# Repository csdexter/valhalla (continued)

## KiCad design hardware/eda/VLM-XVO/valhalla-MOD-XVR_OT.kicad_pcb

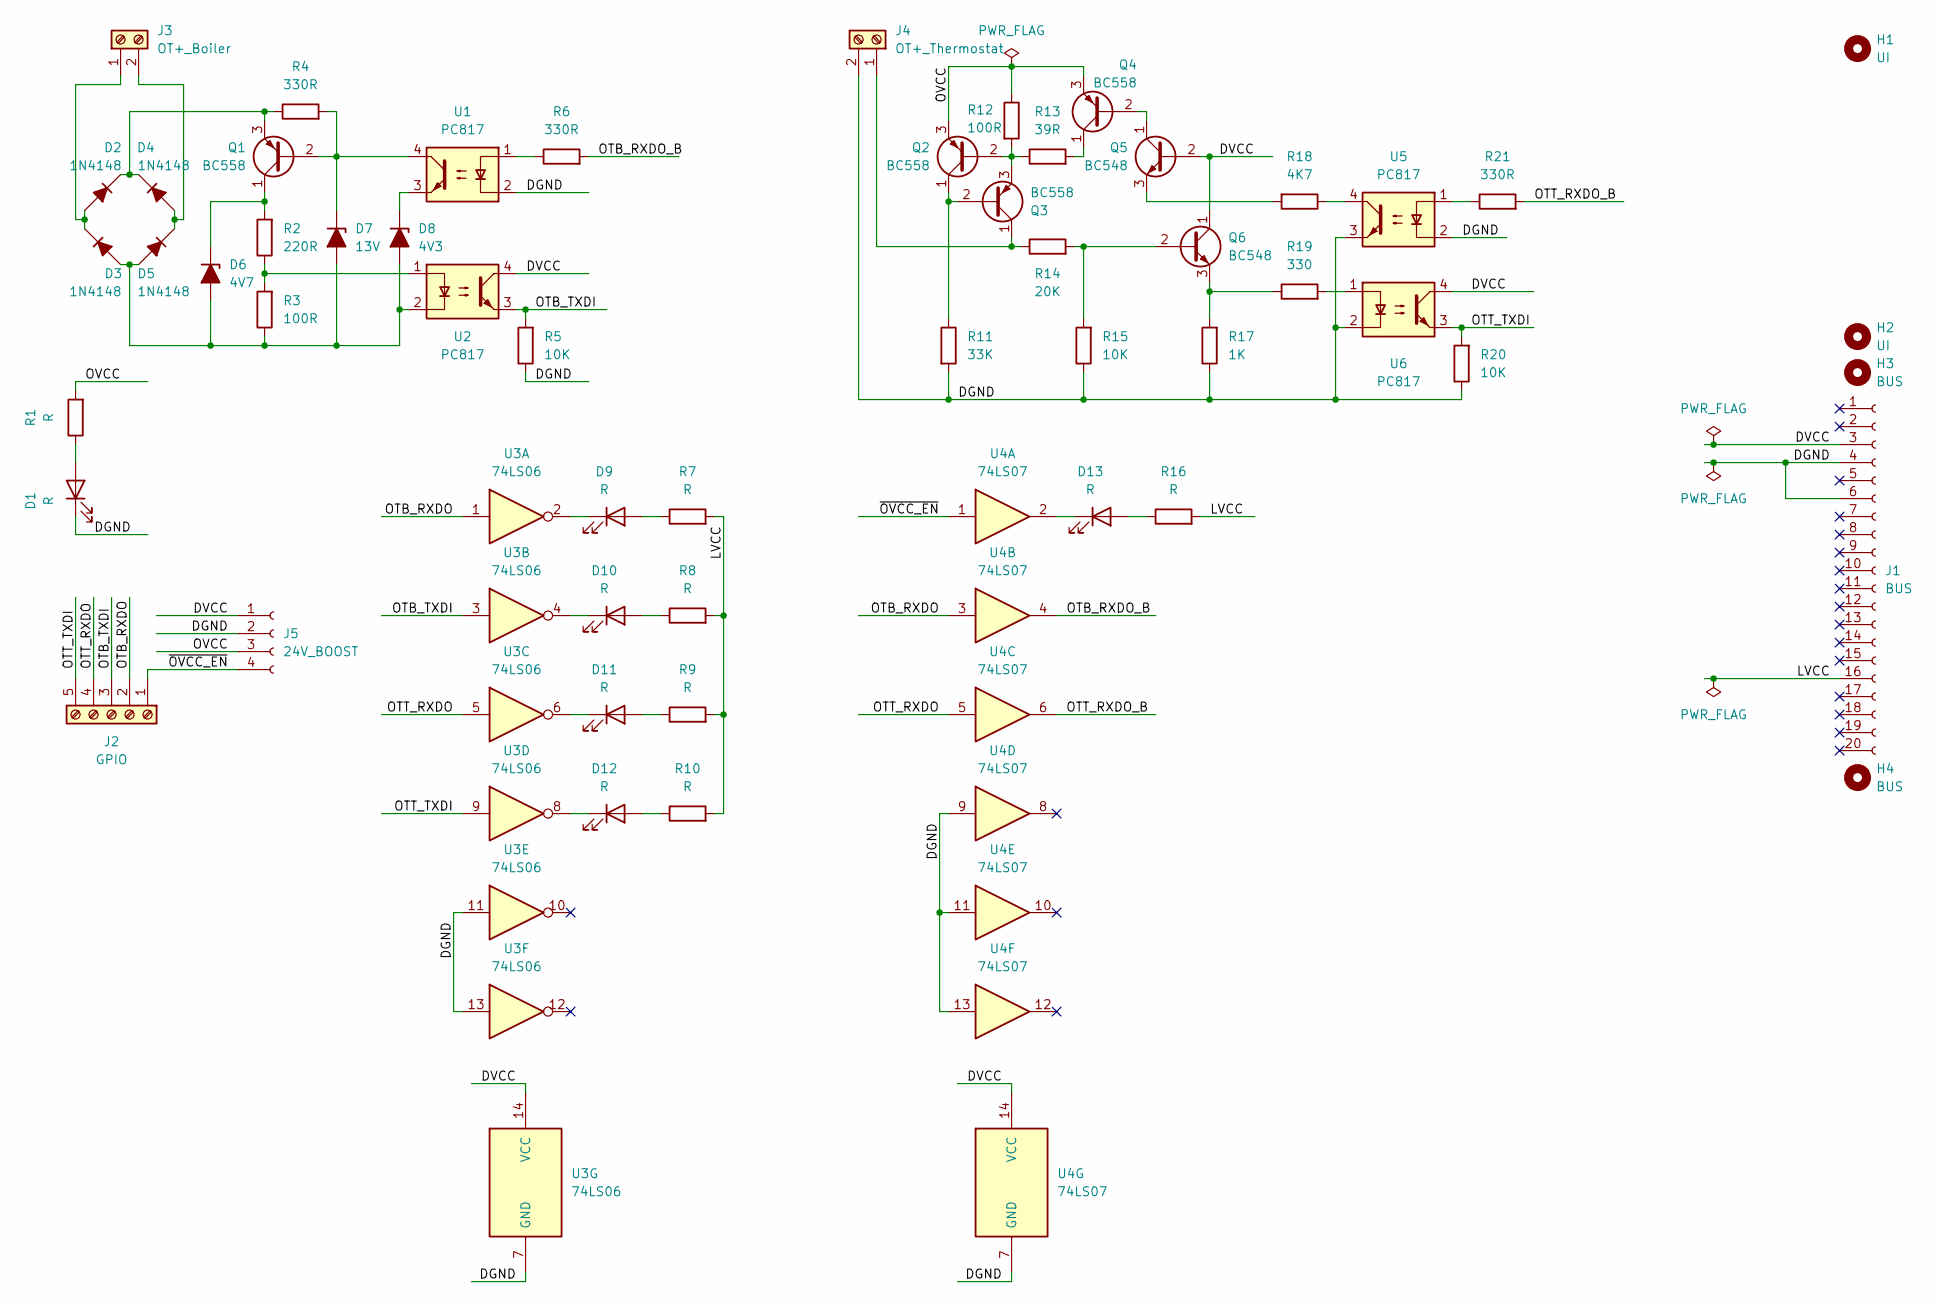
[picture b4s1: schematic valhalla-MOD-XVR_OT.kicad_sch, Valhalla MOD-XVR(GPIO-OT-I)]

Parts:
D1, D9, D10, D11, D12, D13: R; LED_D3.0mm_Horizontal_O1.27mm_Z2.0mm
D2, D3, D4, D5: 1N4148; D_DO-35_SOD27_P7.62mm_Horizontal
D6: 4V7; D_DO-35_SOD27_P7.62mm_Horizontal
D7: 13V; D_DO-35_SOD27_P7.62mm_Horizontal
D8: 4V3; D_DO-35_SOD27_P7.62mm_Horizontal
H1, H2: UI; MountingHole_3.2mm_M3_ISO7380
H3, H4: BUS; MountingHole_3.2mm_M3_ISO7380
J1: BUS; PinSocket_2x10_P2.54mm_Vertical
J2: GPIO; TerminalBlock_Phoenix_MPT-0,5-5-2.54_1x05_P2.54mm_Horizontal
J3: OT+_Boiler; TerminalBlock_Phoenix_MKDS-3-2-5.08_1x02_P5.08mm_Horizontal
J4: OT+_Thermostat; TerminalBlock_Phoenix_MKDS-3-2-5.08_1x02_P5.08mm_Horizontal
J5: 24V_BOOST; PinSocket_1x04_P2.54mm_Vertical
Q1, Q2, Q3, Q4: BC558; TO-92L
Q5, Q6: BC548; TO-92L
R1, R7, R8, R9, R10, R16: R; R_Axial_DIN0207_L6.3mm_D2.5mm_P5.08mm_Vertical
R2: 220R; R_Axial_DIN0207_L6.3mm_D2.5mm_P5.08mm_Vertical
R3, R12: 100R; R_Axial_DIN0207_L6.3mm_D2.5mm_P5.08mm_Vertical
R4, R6, R21: 330R; R_Axial_DIN0207_L6.3mm_D2.5mm_P5.08mm_Vertical
R5, R15, R20: 10K; R_Axial_DIN0207_L6.3mm_D2.5mm_P5.08mm_Vertical
R11: 33K; R_Axial_DIN0207_L6.3mm_D2.5mm_P5.08mm_Vertical
R13: 39R; R_Axial_DIN0207_L6.3mm_D2.5mm_P5.08mm_Vertical
R14: 20K; R_Axial_DIN0207_L6.3mm_D2.5mm_P5.08mm_Vertical
R17: 1K; R_Axial_DIN0207_L6.3mm_D2.5mm_P5.08mm_Vertical
R18: 4K7; R_Axial_DIN0207_L6.3mm_D2.5mm_P5.08mm_Vertical
R19: 330; R_Axial_DIN0207_L6.3mm_D2.5mm_P5.08mm_Vertical
U1, U2, U5, U6: PC817; DIP-4_W7.62mm
U3: 74LS06; DIP-14_W7.62mm
U4: 74LS07; DIP-14_W7.62mm

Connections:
/DGND: D1.1 (K), J1.4, J1.6, J4.2, J5.2, R5.1, R11.2, R15.1, R17.1, R20.1, U1.2, U3.7 (GND), U3.11, U3.13, U4.7 (GND), U4.9, U4.11, U4.13, U5.2, U5.3, U6.2
/DVCC: J1.3, J5.1, Q5.2 (B), Q6.1 (C), U2.4, U3.14 (VCC), U4.14 (VCC), U6.4
/LVCC: J1.16, R7.2, R8.2, R9.2, R10.2, R16.2
/OTB_RXDO: J2.2, U3.1, U4.3
/OTB_RXDO_B: R6.2, U4.4
/OTB_TXDI: J2.3, R5.2, U2.3, U3.3
/OTT_RXDO: J2.4, U3.5, U4.5
/OTT_RXDO_B: R21.2, U4.6
/OTT_TXDI: J2.5, R20.2, U3.9, U6.3
/OVCC: J5.3, Q2.3 (E), Q4.3 (E), R1.2, R12.1
/~OVCC_EN: J2.1, J5.4, U4.1
unnamed: D1.2 (A), R1.1
unnamed: D2.2 (A), D3.1 (K), J3.1
unnamed: D2.1 (K), D4.1 (K), Q1.3 (E), R4.1
unnamed: D3.2 (A), D5.2 (A), D6.2 (A), D7.2 (A), D8.2 (A), R3.1, U2.2
unnamed: D4.2 (A), D5.1 (K), J3.2
unnamed: D6.1 (K), Q1.1 (C), R2.2
unnamed: D7.1 (K), Q1.2 (B), R4.2, U1.4
unnamed: D8.1 (K), U1.3
unnamed: D9.2 (A), R7.1
unnamed: D9.1 (K), U3.2
unnamed: D10.2 (A), R8.1
unnamed: D10.1 (K), U3.4
unnamed: D11.2 (A), R9.1
unnamed: D11.1 (K), U3.6
unnamed: D12.2 (A), R10.1
unnamed: D12.1 (K), U3.8
unnamed: D13.2 (A), R16.1
unnamed: D13.1 (K), U4.2
unnamed: J4.1, Q3.1 (C), R14.1
unnamed: Q2.2 (B), Q3.3 (E), R12.2, R13.1
unnamed: Q2.1 (C), Q3.2 (B), R11.1
unnamed: Q4.2 (B), Q5.1 (C)
unnamed: Q4.1 (C), R13.2
unnamed: Q5.3 (E), R18.2
unnamed: Q6.2 (B), R14.2, R15.2
unnamed: Q6.3 (E), R17.2, R19.1
unnamed: R2.1, R3.2, U2.1
unnamed: R6.1, U1.1
unnamed: R18.1, U5.4
unnamed: R19.2, U6.1
unnamed: R21.1, U5.1

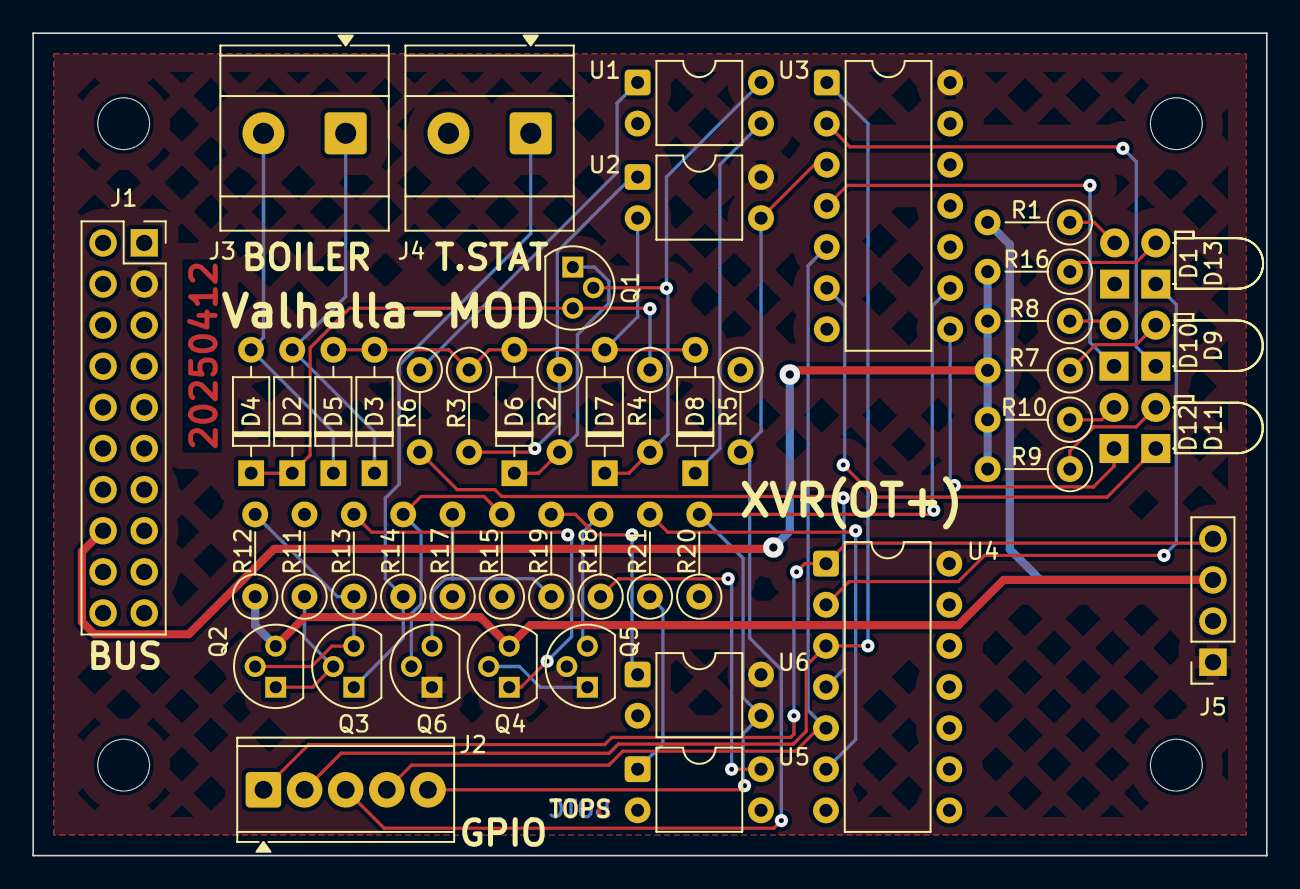
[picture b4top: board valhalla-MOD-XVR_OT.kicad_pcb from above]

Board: 2 copper layers, 76.2 x 50.8 mm, 55 parts (0 on the bottom side), 42 nets.

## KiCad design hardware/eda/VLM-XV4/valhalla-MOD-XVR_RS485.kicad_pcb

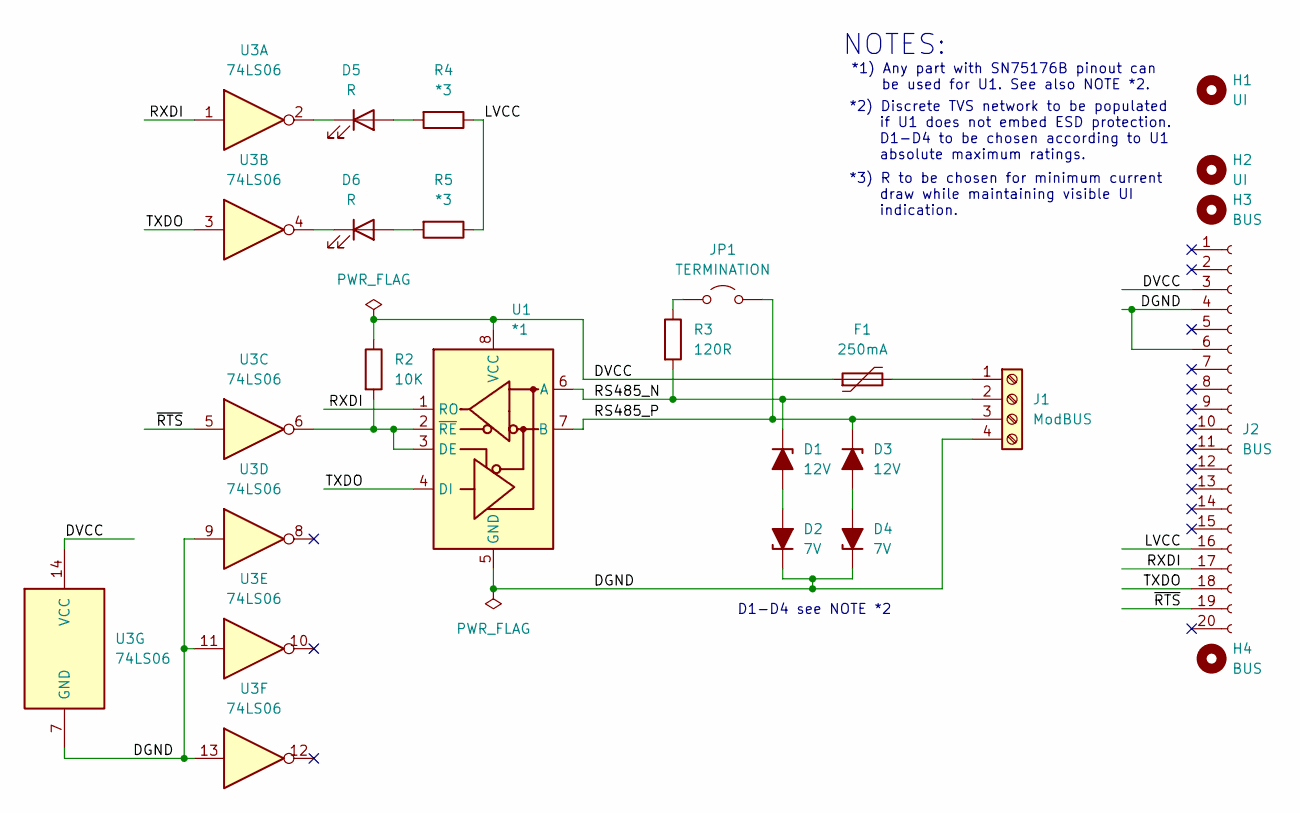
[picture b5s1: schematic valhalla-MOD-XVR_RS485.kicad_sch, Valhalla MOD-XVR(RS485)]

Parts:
D1, D3: 12V; D_DO-41_SOD81_P10.16mm_Horizontal
D2, D4: 7V; D_DO-41_SOD81_P10.16mm_Horizontal
D5, D6: R; LED_D3.0mm_Horizontal_O1.27mm_Z2.0mm
F1: 250mA; C_Disc_D7.5mm_W4.4mm_P5.00mm
H1, H2: UI; MountingHole_3.2mm_M3_ISO7380
H3, H4: BUS; MountingHole_3.2mm_M3_ISO7380
J1: ModBUS; TerminalBlock_Phoenix_MKDS-3-4-5.08_1x04_P5.08mm_Horizontal
J2: BUS; PinSocket_2x10_P2.54mm_Vertical
JP1: TERMINATION; PinHeader_1x02_P2.54mm_Vertical
R2: 10K; R_Axial_DIN0207_L6.3mm_D2.5mm_P5.08mm_Vertical
R3: 120R; R_Axial_DIN0207_L6.3mm_D2.5mm_P5.08mm_Vertical
R4, R5: *3; R_Axial_DIN0207_L6.3mm_D2.5mm_P5.08mm_Vertical
U1: *1; DIP-8_W7.62mm
U3: 74LS06; DIP-14_W7.62mm

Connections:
/DGND: D2.1 (K), D4.1 (K), J1.4, J2.4, J2.6, U1.5 (GND), U3.7 (GND), U3.9, U3.11, U3.13
/DVCC: F1.1, J2.3, R2.1, U1.8 (VCC), U3.14 (VCC)
/LVCC: J2.16, R4.1, R5.1
/RS485_N: D1.1 (K), J1.2, R3.2, U1.6 (A)
/RS485_P: D3.1 (K), J1.3, JP1.2 (B), U1.7 (B)
/RXDI: J2.17, U1.1 (RO), U3.1
/TXDO: J2.18, U1.4 (DI), U3.3
/~RTS: J2.19, U3.5
unnamed: D1.2 (A), D2.2 (A)
unnamed: D3.2 (A), D4.2 (A)
unnamed: D5.2 (A), R4.2
unnamed: D5.1 (K), U3.2
unnamed: D6.2 (A), R5.2
unnamed: D6.1 (K), U3.4
unnamed: F1.2, J1.1
unnamed: JP1.1 (A), R3.1
unnamed: R2.2, U1.2 (~RE), U1.3 (DE), U3.6

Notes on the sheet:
*2) Discrete TVS network to be populated if U1 does not embed ESD protection. D1-D4 to be chosen according to U1 absolute maximum ratings.
*3) R to be chosen for minimum current draw while maintaining visible UI indication.
*1) Any part with SN75176B pinout can be used for U1. See also NOTE *2.
D1-D4 see NOTE *2
NOTES:

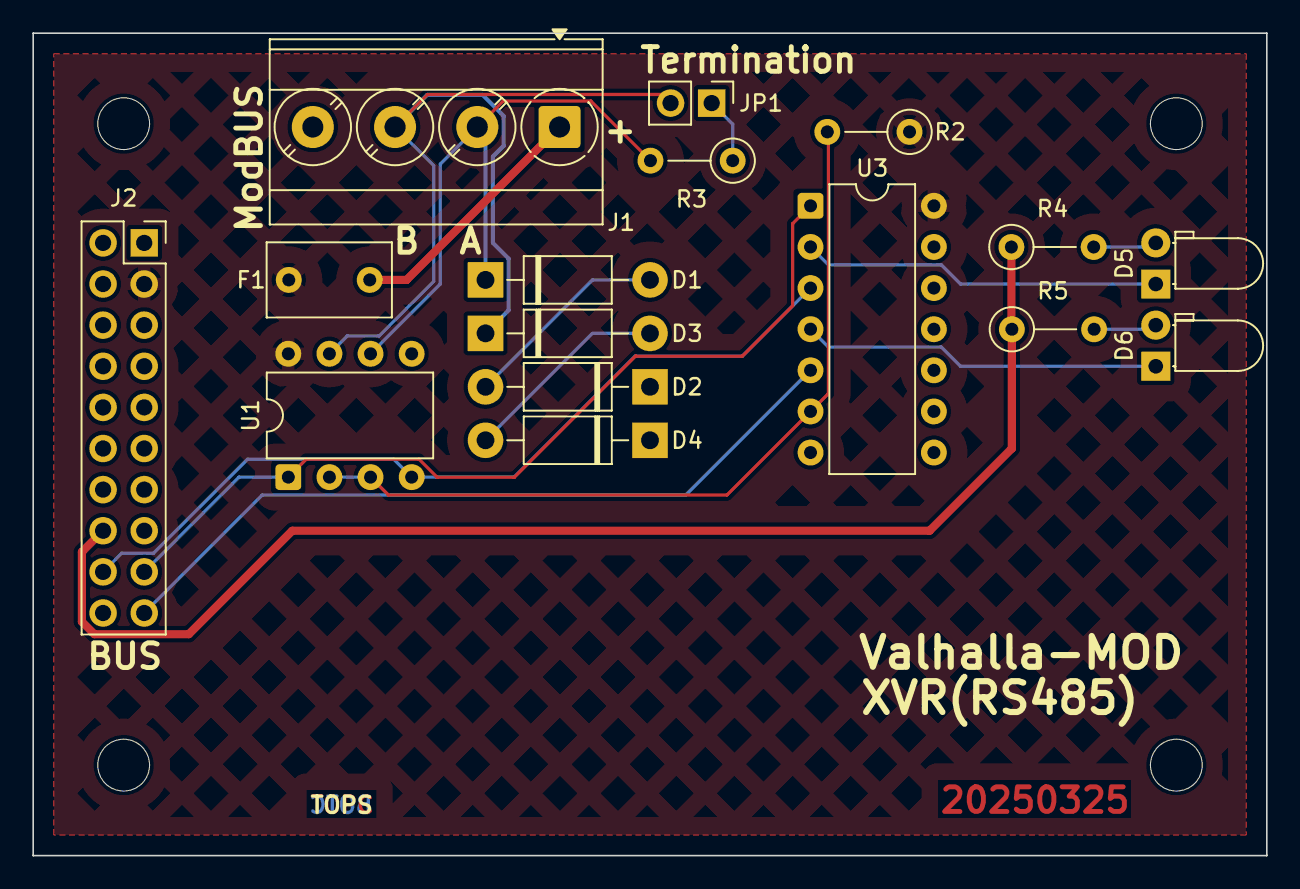
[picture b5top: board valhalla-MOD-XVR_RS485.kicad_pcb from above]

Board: 2 copper layers, 76.2 x 50.8 mm, 20 parts (0 on the bottom side), 17 nets.

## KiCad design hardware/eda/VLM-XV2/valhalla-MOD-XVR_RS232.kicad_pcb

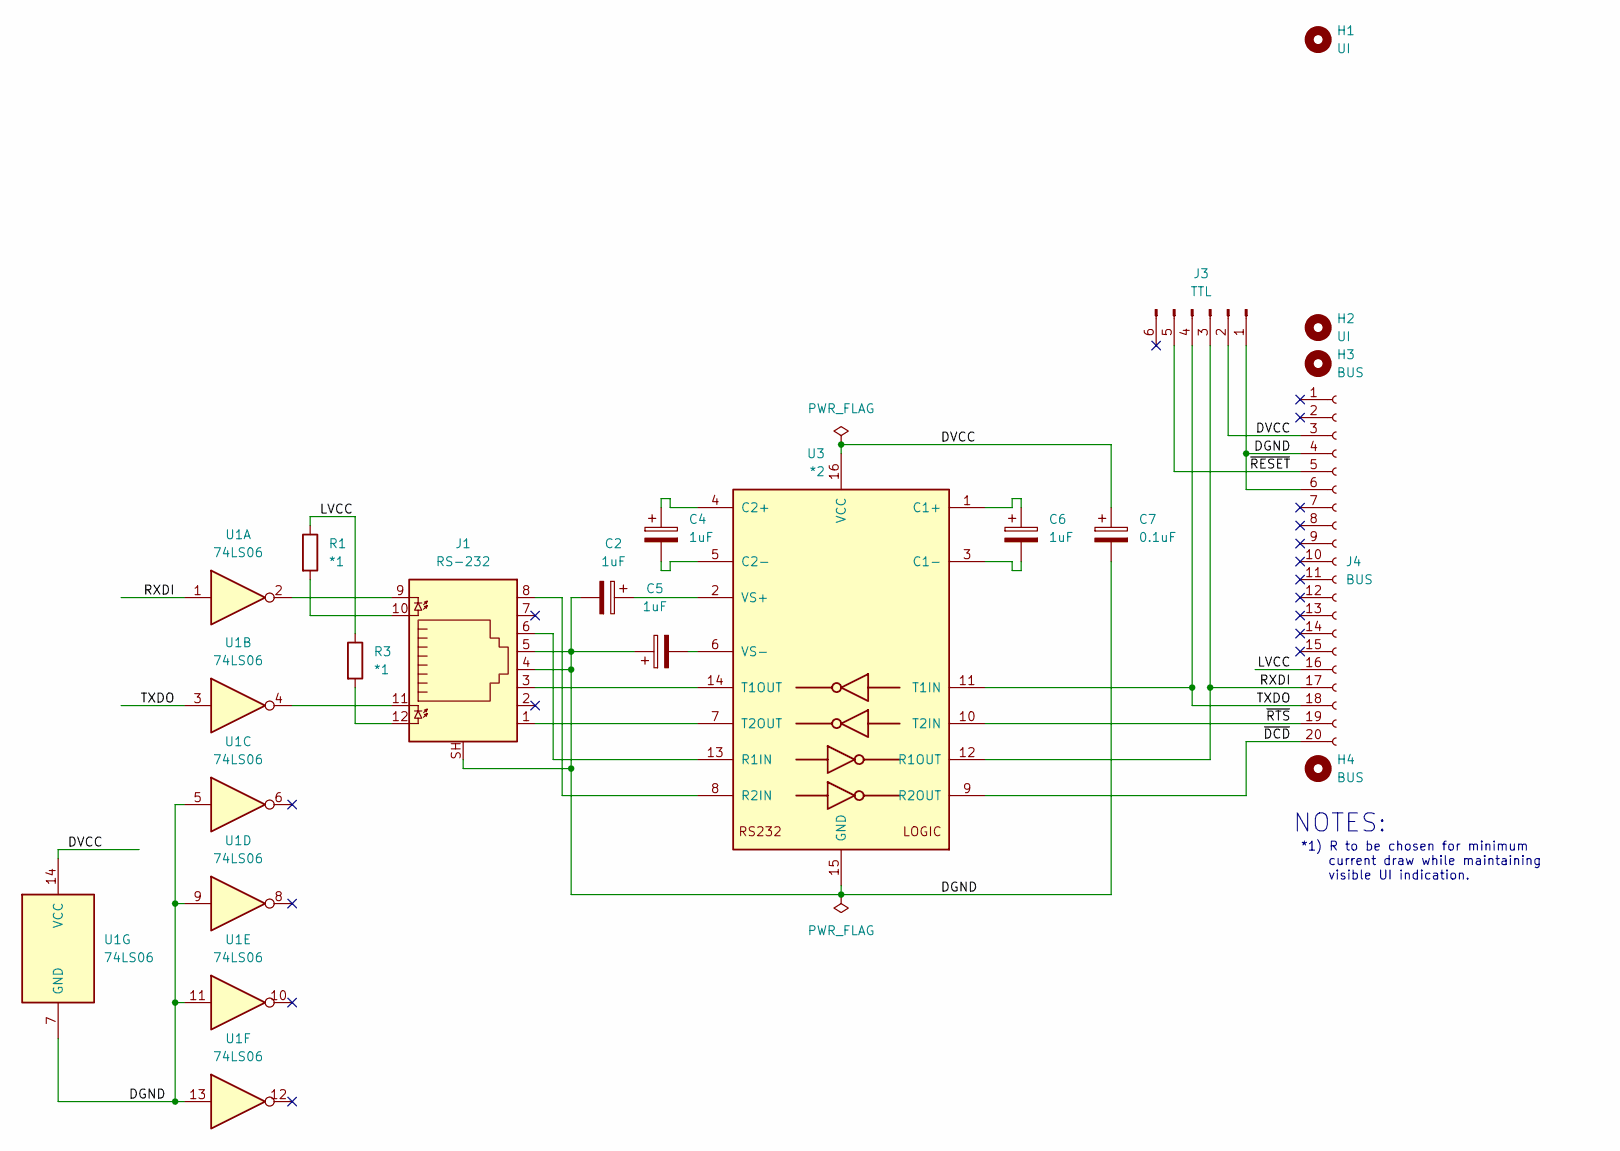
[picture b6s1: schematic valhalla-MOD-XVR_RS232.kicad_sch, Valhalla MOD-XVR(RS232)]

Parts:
C2, C4, C5, C6: 1uF; CP_Radial_D5.0mm_P2.00mm
C7: 0.1uF; C_Rect_L7.2mm_W4.5mm_P5.00mm_FKS2_FKP2_MKS2_MKP2
H1, H2: UI; MountingHole_3.2mm_M3_ISO7380
H3, H4: BUS; MountingHole_3.2mm_M3_ISO7380
J1: RS-232; RJ45_Amphenol_RJHSE538X
J3: TTL; PinHeader_2x03_P2.54mm_Horizontal
J4: BUS; PinSocket_2x10_P2.54mm_Vertical
R1, R3: *1; R_Axial_DIN0207_L6.3mm_D2.5mm_P5.08mm_Vertical
U1: 74LS06
U3: *2; DIP-16_W7.62mm

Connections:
/DGND: C2.2, C5.1, C7.2, J1.4, J1.5, J1.SH, J3.1, J4.4, J4.6, U1.5, U1.7 (GND), U1.9, U1.11, U1.13, U3.15 (GND)
/DVCC: C7.1, J3.2, J4.3, U1.14 (VCC), U3.16 (VCC)
/LVCC: J4.16, R1.1, R3.1
/RXDI: J3.3, J4.17, U1.1, U3.12 (R1OUT)
/TXDO: J3.4, J4.18, U1.3, U3.11 (T1IN)
/~DCD: J4.20, U3.9 (R2OUT)
/~RESET: J3.5, J4.5
/~RTS: J4.19, U3.10 (T2IN)
unnamed: J1.9, U1.2
unnamed: J1.10, R1.2
unnamed: J1.11, U1.4
unnamed: J1.12, R3.2
unnamed: C6.1, U3.1 (C1+)
unnamed: C6.2, U3.3 (C1-)
unnamed: C4.1, U3.4 (C2+)
unnamed: C4.2, U3.5 (C2-)
unnamed: J1.6, U3.13 (R1IN)
unnamed: J1.8, U3.8 (R2IN)
unnamed: J1.3, U3.14 (T1OUT)
unnamed: J1.1, U3.7 (T2OUT)
unnamed: C2.1, U3.2 (VS+)
unnamed: C5.2, U3.6 (VS-)

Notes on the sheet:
*1) R to be chosen for minimum current draw while maintaining visible UI indication.
NOTES:

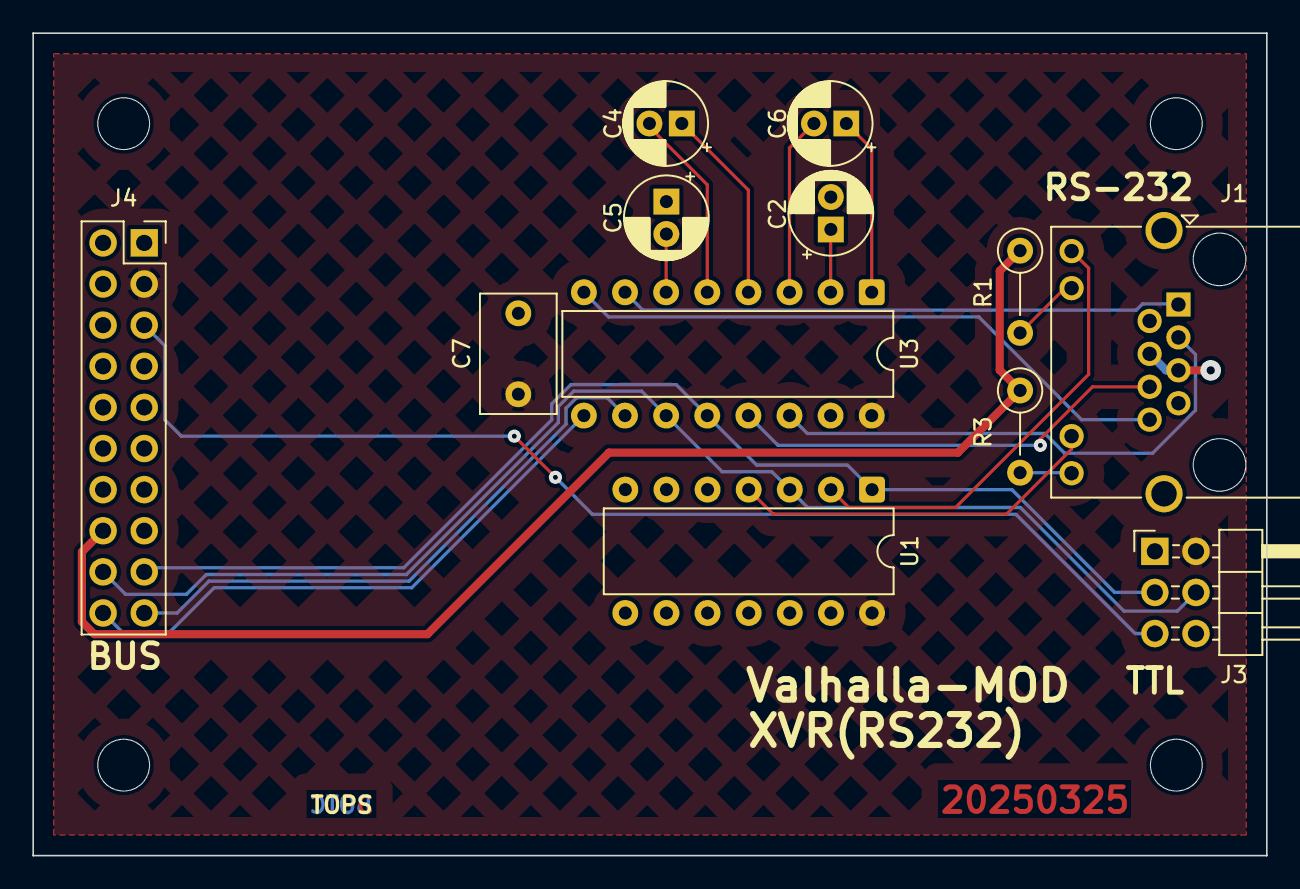
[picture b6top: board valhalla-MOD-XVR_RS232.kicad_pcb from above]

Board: 2 copper layers, 76.2 x 50.8 mm, 16 parts (0 on the bottom side), 22 nets.

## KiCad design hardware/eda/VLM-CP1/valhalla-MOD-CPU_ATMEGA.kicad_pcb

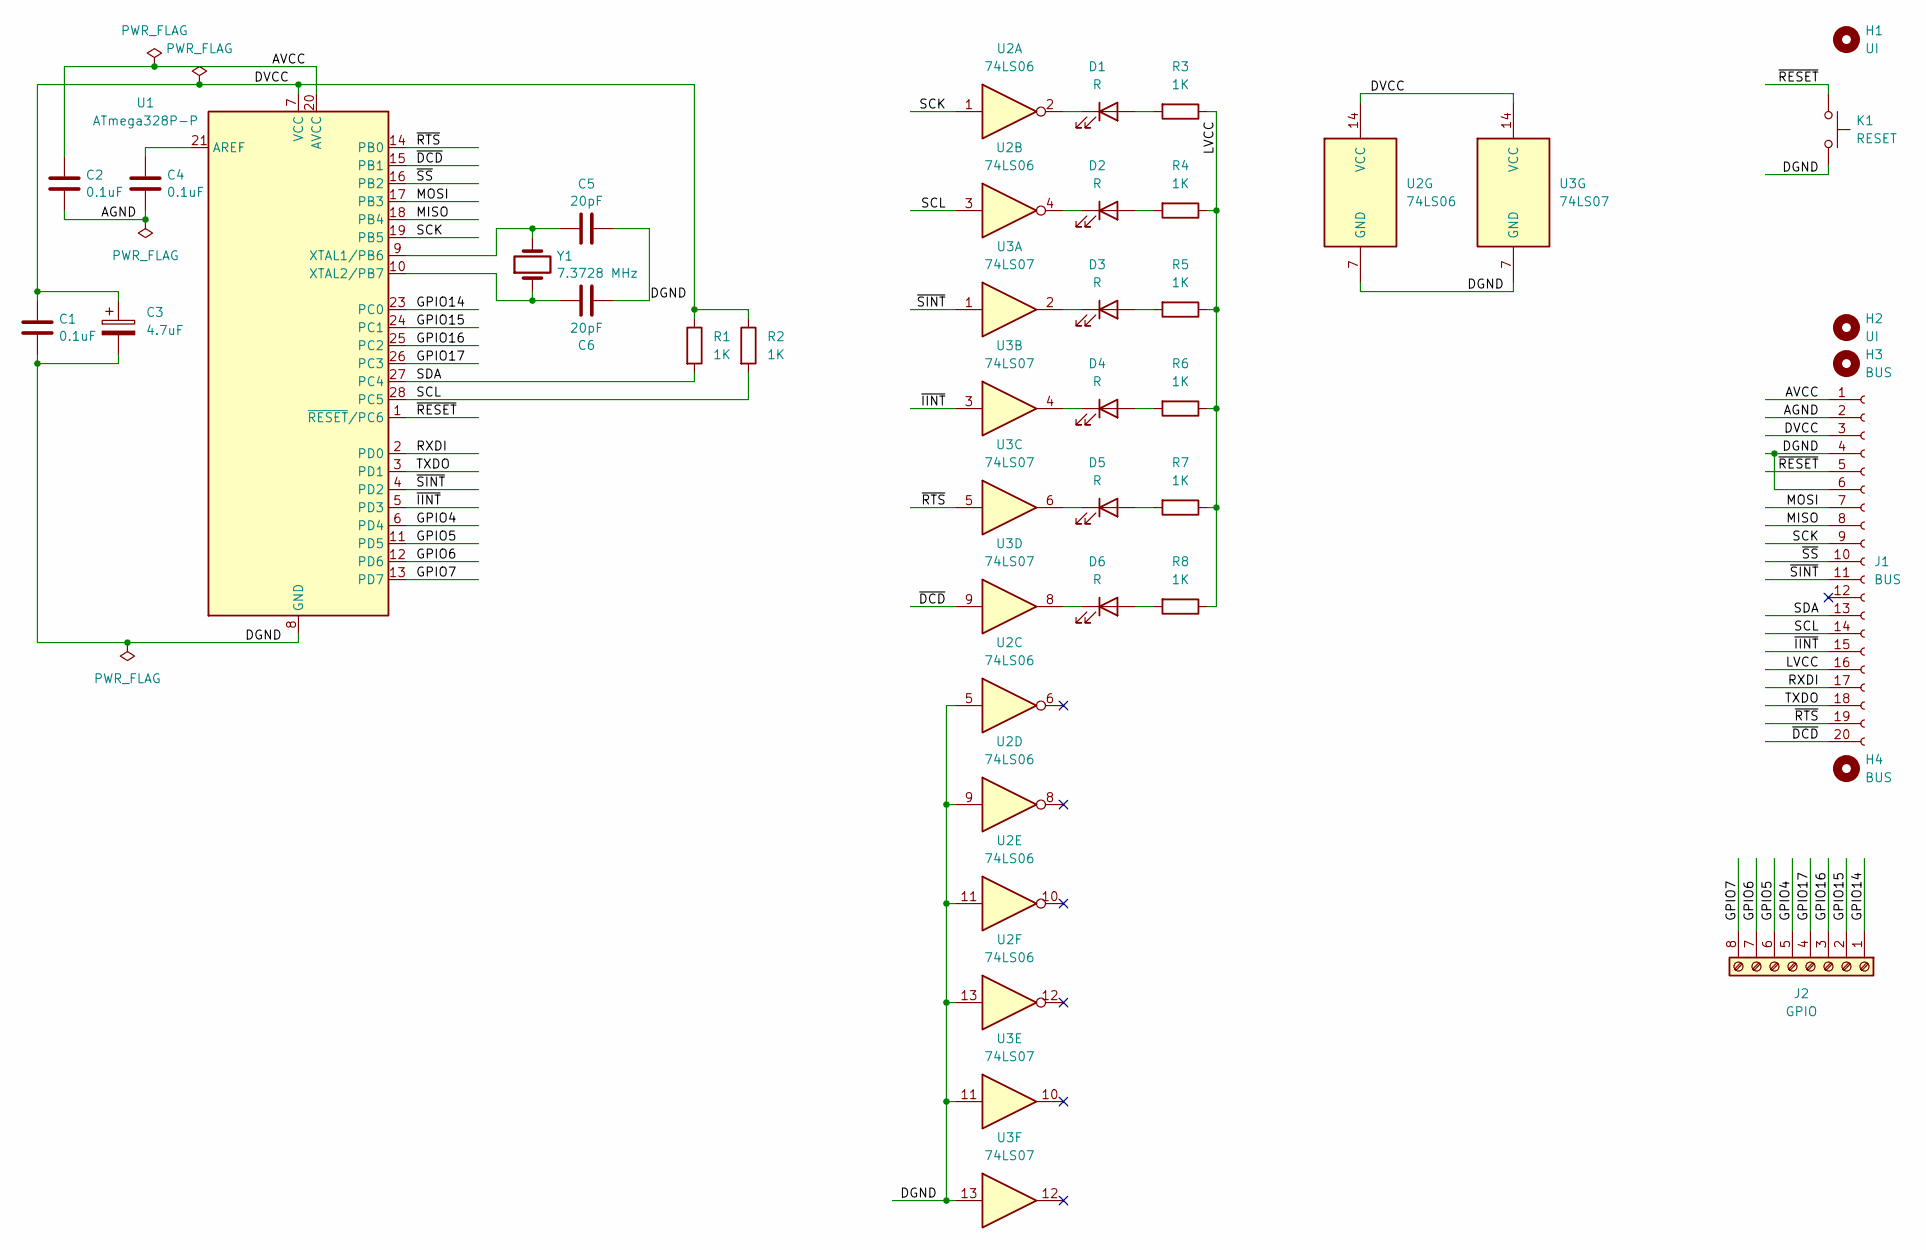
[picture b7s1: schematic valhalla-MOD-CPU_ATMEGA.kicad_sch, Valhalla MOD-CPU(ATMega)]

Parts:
C1, C2, C4: 0.1uF; C_Rect_L4.6mm_W2.0mm_P2.50mm_MKS02_FKP02
C3: 4.7uF; CP_Radial_D5.0mm_P2.50mm
C5, C6: 20pF; C_Disc_D5.0mm_W2.5mm_P5.00mm
D1, D2, D3, D4, D5, D6: R; LED_D3.0mm_Horizontal_O1.27mm_Z2.0mm
H1, H2: UI; MountingHole_3.2mm_M3_ISO7380
H3, H4: BUS; MountingHole_3.2mm_M3_ISO7380
J1: BUS; PinSocket_2x10_P2.54mm_Vertical
J2: GPIO; TerminalBlock_Phoenix_MPT-0,5-8-2.54_1x08_P2.54mm_Horizontal
K1: RESET; SW_Tactile_SKHH_Angled
R1, R2, R3, R4, R5, R6, R7, R8: 1K; R_Axial_DIN0207_L6.3mm_D2.5mm_P5.08mm_Vertical
U1: ATmega328P-P; DIP-28_W7.62mm
U2: 74LS06; DIP-14_W7.62mm
U3: 74LS07; DIP-14_W7.62mm
Y1: 7.3728 MHz; Crystal_HC49-4H_Vertical

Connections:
/AGND: C2.2, C4.2, J1.2
/AVCC: C2.1, J1.1, U1.20 (AVCC)
/DGND: C1.2, C3.2, C5.2, C6.2, J1.4, J1.6, K1.2, U1.8 (GND), U1.22 (GND), U2.5, U2.7 (GND), U2.9, U2.11, U2.13, U3.7 (GND), U3.11, U3.13
/DVCC: C1.1, C3.1, J1.3, R1.1, R2.1, U1.7 (VCC), U2.14 (VCC), U3.14 (VCC)
/GPIO4: J2.5, U1.6 (PD4)
/GPIO5: J2.6, U1.11 (PD5)
/GPIO6: J2.7, U1.12 (PD6)
/GPIO7: J2.8, U1.13 (PD7)
/GPIO14: J2.1, U1.23 (PC0)
/GPIO15: J2.2, U1.24 (PC1)
/GPIO16: J2.3, U1.25 (PC2)
/GPIO17: J2.4, U1.26 (PC3)
/LVCC: J1.16, R3.1, R4.1, R5.1, R6.1, R7.1, R8.1
/MISO: J1.8, U1.18 (PB4)
/MOSI: J1.7, U1.17 (PB3)
/RXDI: J1.17, U1.2 (PD0)
/SCK: J1.9, U1.19 (PB5), U2.1
/SCL: J1.14, R2.2, U1.28 (PC5), U2.3
/SDA: J1.13, R1.2, U1.27 (PC4)
/TXDO: J1.18, U1.3 (PD1)
/~DCD: J1.20, U1.15 (PB1), U3.9
/~IINT: J1.15, U1.5 (PD3), U3.3
/~RESET: J1.5, K1.1, U1.1 (~RESET/PC6)
/~RTS: J1.19, U1.14 (PB0), U3.5
/~SINT: J1.11, U1.4 (PD2), U3.1
/~SS: J1.10, U1.16 (PB2)
unnamed: D1.2 (A), R3.2
unnamed: D1.1 (K), U2.2
unnamed: D2.2 (A), R4.2
unnamed: D2.1 (K), U2.4
unnamed: D3.2 (A), R5.2
unnamed: D3.1 (K), U3.2
unnamed: D4.2 (A), R6.2
unnamed: D4.1 (K), U3.4
unnamed: D5.2 (A), R7.2
unnamed: D5.1 (K), U3.6
unnamed: D6.2 (A), R8.2
unnamed: D6.1 (K), U3.8
unnamed: C4.1, U1.21 (AREF)
unnamed: C5.1, U1.9 (XTAL1/PB6), Y1.2
unnamed: C6.1, U1.10 (XTAL2/PB7), Y1.1

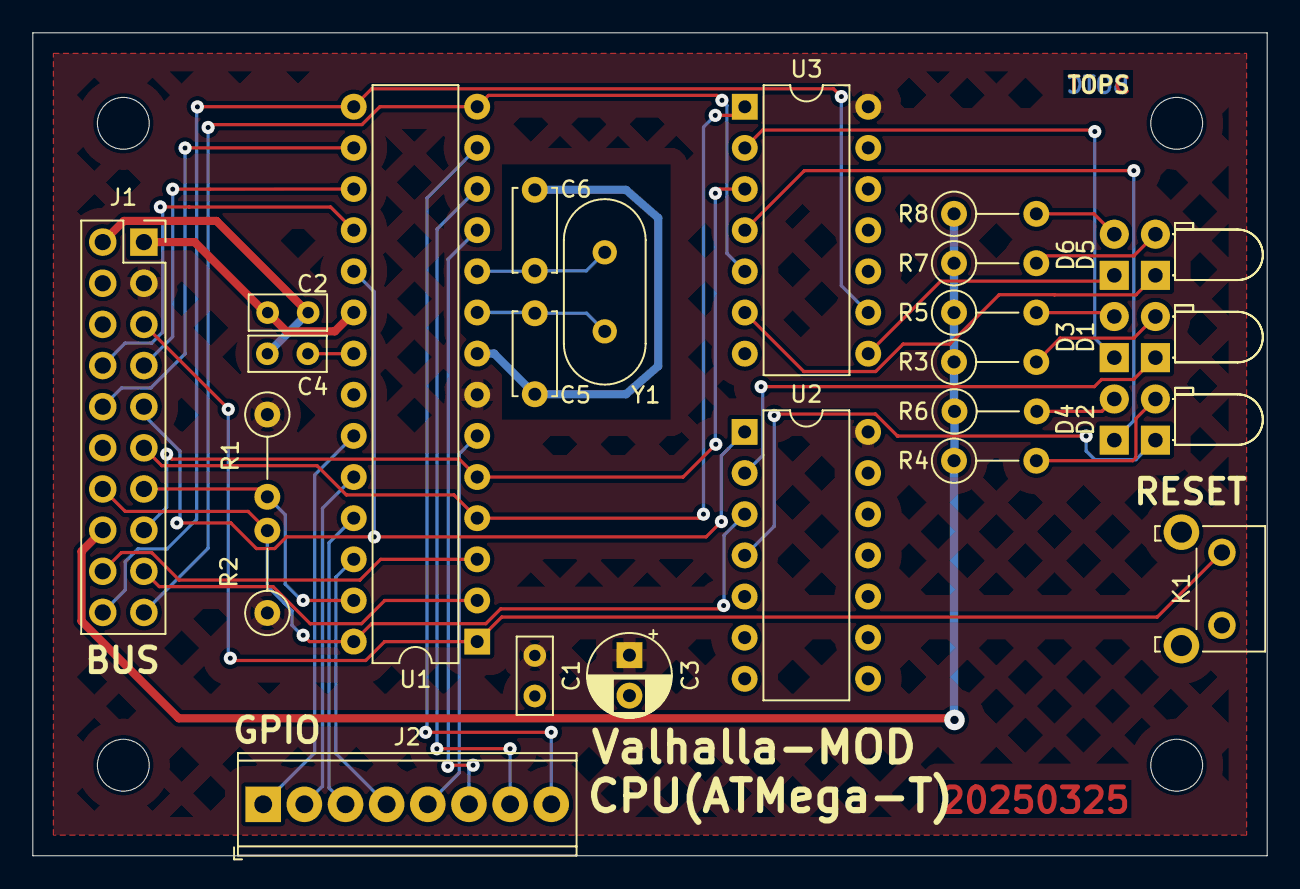
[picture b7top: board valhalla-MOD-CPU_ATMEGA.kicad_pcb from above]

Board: 2 copper layers, 76.2 x 50.8 mm, 31 parts (0 on the bottom side), 41 nets.

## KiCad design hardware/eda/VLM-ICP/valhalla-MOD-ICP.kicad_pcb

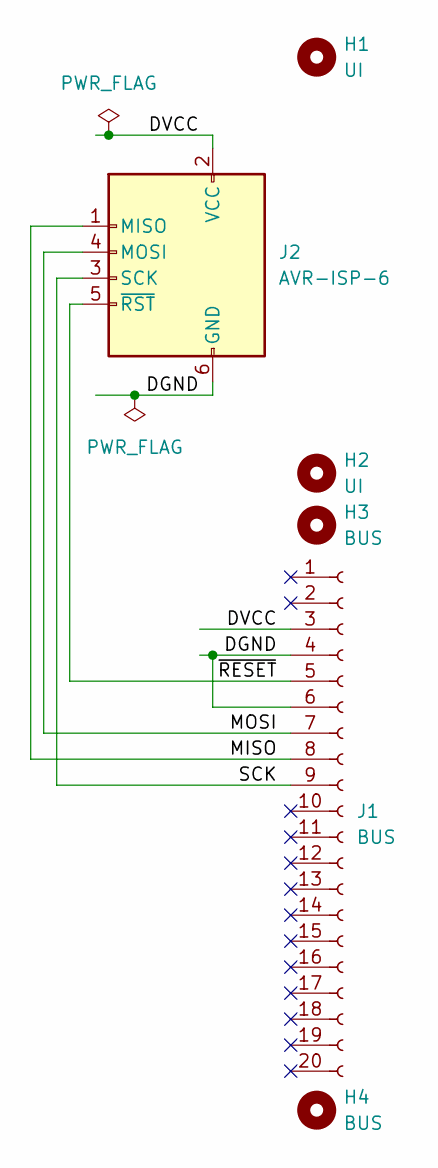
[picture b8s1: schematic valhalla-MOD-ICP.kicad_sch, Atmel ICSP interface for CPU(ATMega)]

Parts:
H1, H2: UI; MountingHole_3.2mm_M3_ISO7380
H3, H4: BUS; MountingHole_3.2mm_M3_ISO7380
J1: BUS; PinSocket_2x10_P2.54mm_Vertical
J2: AVR-ISP-6; IDC-Header_2x03_P2.54mm_Horizontal

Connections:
/DGND: J1.4, J1.6, J2.6 (GND)
/DVCC: J1.3, J2.2 (VCC)
/MISO: J1.8, J2.1 (MISO)
/MOSI: J1.7, J2.4 (MOSI)
/SCK: J1.9, J2.3 (SCK)
/~RESET: J1.5, J2.5 (~RST)

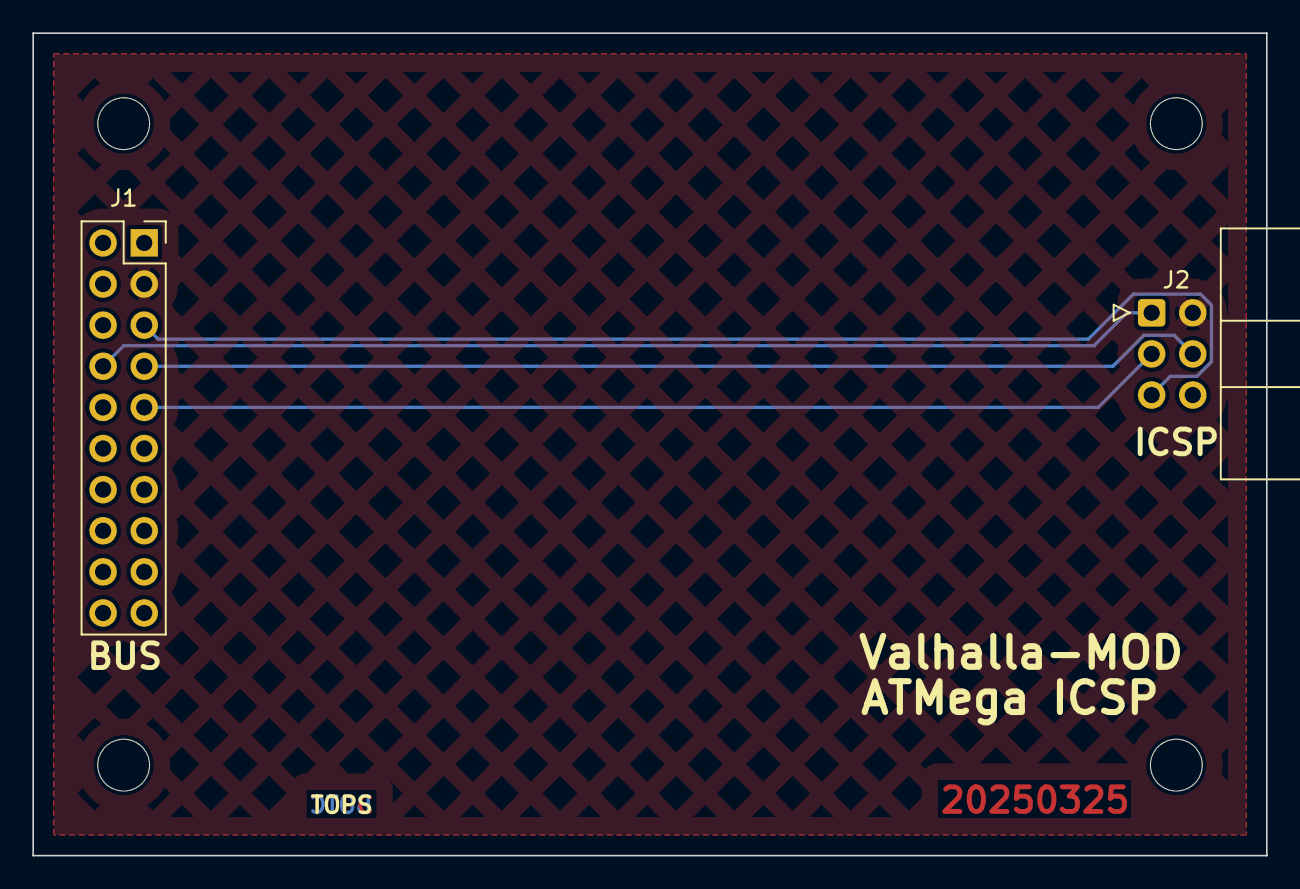
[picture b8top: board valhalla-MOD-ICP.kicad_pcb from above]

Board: 2 copper layers, 76.2 x 50.8 mm, 6 parts (0 on the bottom side), 6 nets.
